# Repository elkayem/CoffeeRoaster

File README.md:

# COFFEE ROASTER

This repository contains the code for a PID controlled coffee roaster, run on a Teensy 3.5/3.6 development board.

A quick summary of the features:
* *Auto Mode* which will control the temperature (bean or environment) and fan speed to a settable profile.  
* *Manual Mode* where temperature and fan speed can be controlled in real time.
* Measured temperatures, set value, fan speed, and heater duty cycle saved to an SD card as a CSV file at 2 Hz while roasting.  See image above showing data from a roast.  I've also included a python script used to plot this data from the SD card.  The script requires the python module "matplotlib".  
* DC Fan PWM control.  (The MOSFET on the PCB can handle quite a bit of current.  I am using a 22 Amp, 260 Watt fan, and the MOSFET has additional headroom beyond that).    
* The roasting profile can be set as a sequence of up to 9 segments.  The set temperature and fan speed are linearly interpolated from one segment to the next.  This profile can be set and saved to EEPROM via the LCD screen interface.  
* Separate tuneable PID values for the environment temperature and bean temperature.  A tuning mode for each controller is available allowing one to monitor the step response and tune the gains in real time.
* (Optional) interface with [Artisan Roaster Scope](https://artisan-scope.org/).  The roast can be logged by Artisan in Auto or Manual mode, or even have Artisan control the set temperature and fan speed in Manual mode.  

I loosely based my roaster build off of a few of the fluid bed roasters over at the Home Roaster's forum using a Pyrex Bake-A-Round baking tube and inverted cocktail shaker lid.  For example, see Old Gear Head's fluid bed roaster design at: https://forum.homeroasters.org/forum/viewthread.php?thread_id=2207.   

Here are the parts needed for the electronics board:
* PCB (Order using gerber files in Eagle directory, or ask me and I'll send you one for a small amount.  Alternatively, the electronics can be soldered to a stripboard)
* Teensy 3.5 (or 3.6), $24.25 from pjrc.com + MicroSD card
* 2x MAX31855KASA+ thermocouple ICs ($5 each)
* 4x SMD ferrite beads (I used 470 ohms 0805 package)
* 3x BSS138 MOSFET transistors
* IRLB8721PBF MOSFET + heat sink (very important!!)
* 2N3904 transistor
* SB1245 Schottky diode
* 7805 5V regulator 
* Various resistors and capacitors (see schematic in Eagle directory)

Here are the additional parts I used:
* 20x4 character I2C LCD screen ($9 on eBay)
* Two K-type thermocouples
* Metal thermocouple probe shield (e.g., look for the 5mm x 50 mm thermocouple probe from Uxcell on Amazon, and cut off the end of the metal shield)
* Fotek SSR-40 DA Solid State Relay + Heat Sink ($12.50 on eBay)
* 12V, 25A power regulated switching power supply ($19 at eBay)
* Pyrex Bake-A-Round baking tube ($20 at eBay)
* Lid from Winco 16-oz coctail shaker, 1.5" and 3.5" diam ($7.50 at Amazon)
* 1.5" x 12" chrome tube ($10 at Amazon)
* HAS-043K 1700 Watt heating element ($22 at Amazon)
* Airhead "Air Pig" 12V, 22 Amp air pump ($42 at Amazon)
* 340 Silicone O-Rings 3.5" diam

A schematic and PCB design (see Eagle folder) is included in this repository.  The Gerber files can be uploaded to a PCB manufacturer (e.g., JLCPCB, SchenZhen2U, or Seeed Studio), typically for a few dollars a board and a minimum order of 5-10 boards.  Alternatively, contact me and I can send you one (without components) at cost plus shipping.  The electronics can also be soldered to a breadboard.  If using a breadboard, you will also need two MAX31855 breakout boards from Adafruit, as well as a logic level converter for the I2C LCD communication.

The DC motor is driven by the 12V power supply, with PWM speed control from the microcontroller.  It is vitally important that a few small capacitors be soldered directly to the motor leads to reduce voltage noise on the DC power, otherwise the inevitable voltage spikes from the DC motor will reset the microcontroller in the middle of your roast.  Not good!  I used a 22 nF capacitor across the leads, and then two 10 nF capacitors from each lead directly to the motor housing.   

The 12V, 22 Amp DC motor I used draws a lot of current, so be sure to use beefy wires (e.g., 14 AWG) all the way to the MOSFET.  Be sure to use a heat sink on the IRLB8721PBF MOSFET.  The wide traces on the back of the PCB are inadequate to handle 22A.  I recommend laying down a heavy layer of solder directly to these traces.  Better yet, solder exposed 14 AWG wire directly to the traces.  See photos above.

I enclosed the DC motor in my own 3D printed case and threw away the pig shaped case on the Airhead "Air Pig".  I've included the 3D printed case model in this repository, which encloses the motor and is sealed with a 3.5" O-ring.  I'm sure the pig shaped case would work too, but don't use the corrugated hose which produces too much drag.  

Two temperature measurements are used.  I placed the Environment Temperature thermocouple close to the center of the chamber in the line of fire of the hot air, and the Bean Temperature probe off to the side and blocked from the upcoming air.  A metal thermocouple shield is used to hold the probes in place.  I purchased a thermocouple probe from Uxcell on Amazon that came with a metal shield, and sawed off the end of the metal shield.  I have included a photograph below showing the thermocouple placement, and a drawing as well.  The bean temperature thermocouple and wires are taped to the top of the thermocouple metal shield using Kapton tape, which allows this thermocouple to register the temperature of the beans descending along the side of the shaker lid, and outside of the stream of hot air.  

I have also included a few 3D printed parts I used, which may be useful.  This repository includes a front panel for the LCD screen, and also the buttresses to hold the Bake-A-Round vertical. 

The plans for a 1/4" ply laser cut case are also included if you have access to a laser cutter.  Or build your own!  

# Artisan Roaster Scope Instructions
Artisan is not required for this roaster, as the Teensy firmware can already track a stored profile and save the roast data to an SD card without an external interface.  I still highly recommend Artisan as it includes additional visual analysis tools. 

**Important Note:** The USB port 5V power *must* be disconnected before attempting to interface with Artisan. There are several ways to do this, described at https://www.pjrc.com/teensy/external_power.html.  The simplest way is to disconnect the 5V pads apart on the bottom of the Teensy board.  I chose a different method in my roaster.  My roaster has a USB panel mount on the outside of the case, with an internal USB cable going from the panel mount to the Teensy.  Since this cable is permanently isntalled inside my case, I chose to clip the red wire inside the cable, sealing off the cut wire with shrink tube to prevent a short.  This avoids the need to modify the Teensy itself.

Coffee Roaster uses the same Artisan communication protocol as a TC4.  To use this Teensy code with Artisan, set up the device as a TC4 in Config>Device on the ET/BT tab.  Check the "Control" and "PID Firmware" checkboxes.  On the Extra Devices tab, set up the ArduinoTC4_34, ArduinoTC4_56 (Label 1 = Heater, Label 2 = Fan), and ArduinoTC4_78 (Label 1 = SV, Label 2 = Ambient).  Check the LCD 1, LCD 2, Curve 1, and Curve 2 checkboxes for ArduinoTC4_56 and _78, but uncheck for _34.  The YouTube video [Artisan Roaster Scope - Setup for TC4](https://youtu.be/0-Co-pXF2NM) walks through the setup procedure.

The above steps are sufficient for logging your roast with Artisan.  To control the roast using Artisan, check out the YouTube video [Artisan Roaster Scope - TC4 PID Control](https://youtu.be/ykuUCXhGAC4).  This video has four parts.  The two parts labeled "Background Follow TC4 PID" and "Ramp/Soak Profile TC4 PID" can be used with this code.  The "Artisan PID" variants are not currently supported.  

If using Artisan to control your roaster, you will also need to set up the DC Fan control. To do this, open the Config>Events dialog, change the first Event name to Fan, go to the Sliders tab, and set the Fan Action to Serial Command, and add the command "DCFAN;{}" to the selection box, without the quotes.

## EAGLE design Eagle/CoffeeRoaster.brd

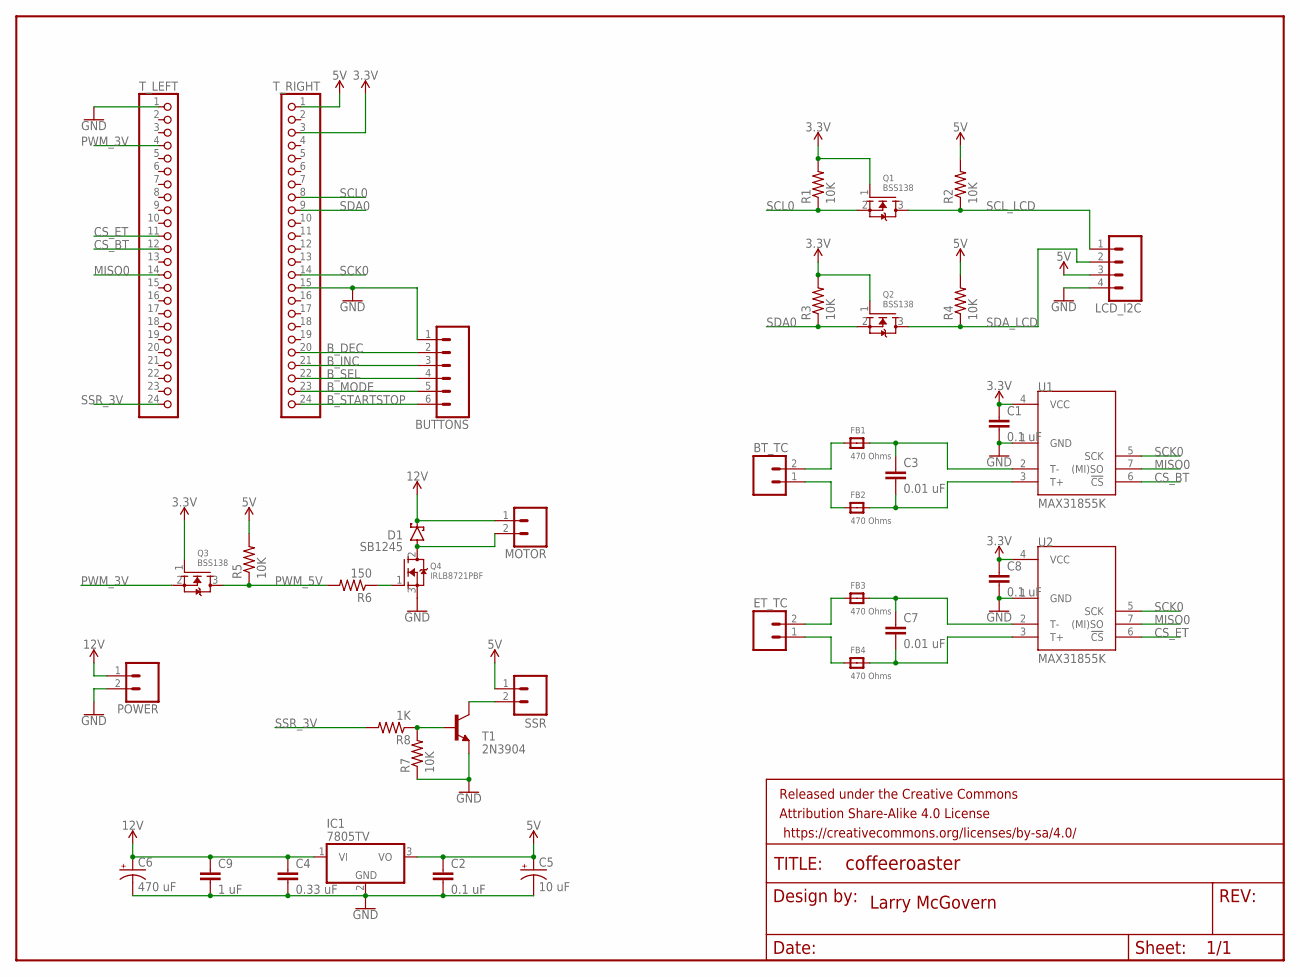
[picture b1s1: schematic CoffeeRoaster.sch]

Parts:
BT_TC: M025MM; SCREWTERMINAL-5MM-2
BUTTONS: CONN_06SILK_FEMALE_PTH; 1X06
C1, C2, C8: 0.1 uF; C050-025X075
C3, C7: 0.01 uF; C050-025X075
C4: 0.33 uF; C050-025X075
C5: 10 uF; E2,5-6
C6: 470 uF; E5-10,5
C9: 1 uF; C050-025X075
D1: SB1245; DO201T15
ET_TC: M025MM; SCREWTERMINAL-5MM-2
FB1, FB2, FB3, FB4: 470 Ohms; _0805
FRAME1: FRAME-LETTER; CREATIVE_COMMONS
IC1: 7805TV; TO220V
LCD_I2C: CONN_04; 1X04
MOTOR: CONN_02PTH4; 1X02_XTRA_BIG
POWER: CONN_02PTH4; 1X02_XTRA_BIG
Q1, Q2, Q3: BSS138; SOT23
Q4: IRLB8721PBF; TO220V
R1, R2, R3, R4, R5, R7: 10K; 0207/10
R6: 150; 0207/10
R8: 1K; 0207/10
SSR: M025MM; SCREWTERMINAL-5MM-2
T1: 2N3904; TO92
T_LEFT: PINHD-1X24; 1X24
T_RIGHT: PINHD-1X24; 1X24
U1, U2: MAX31855K; SO08

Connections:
3.3V: C1.1, C8.1, Q1.1 (G), Q2.1 (G), Q3.1 (G), R1.2, R3.2, T_RIGHT.3, U1.4 (VCC), U2.4 (VCC)
5V: C2.1, C5.+, IC1.3 (VO), LCD_I2C.3, R2.2, R4.2, R5.2, SSR.1, T_RIGHT.1
12V: C4.1, C6.+, C9.1, D1.C, IC1.1 (VI), MOTOR.1, POWER.1
B_DEC: BUTTONS.2, T_RIGHT.20
B_INC: BUTTONS.3, T_RIGHT.21
B_MODE: BUTTONS.5, T_RIGHT.23
B_SEL: BUTTONS.4, T_RIGHT.22
B_STARTSTOP: BUTTONS.6, T_RIGHT.24
CS_BT: T_LEFT.12, U1.6 (!CS)
CS_ET: T_LEFT.11, U2.6 (!CS)
GND: BUTTONS.1, C1.2, C2.2, C4.2, C5.-, C6.-, C8.2, C9.2, IC1.2 (GND), LCD_I2C.4, POWER.2, Q4.3 (S), R7.1, T1.3 (E), T_LEFT.1, T_RIGHT.15, U1.1 (GND), U2.1 (GND)
MISO0: T_LEFT.14, U1.7 ((MI)SO), U2.7 ((MI)SO)
MOT_NEG: D1.A, MOTOR.2, Q4.2 (D)
unnamed: Q4.1 (G), R6.1
unnamed: BT_TC.2, FB1.1
unnamed: ET_TC.2, FB3.1
unnamed: C3.1, FB1.2, U1.2 (T-)
unnamed: BT_TC.1, FB2.1
unnamed: C3.2, FB2.2, U1.3 (T+)
unnamed: C7.1, FB3.2, U2.2 (T-)
unnamed: ET_TC.1, FB4.1
unnamed: C7.2, FB4.2, U2.3 (T+)
unnamed: R7.2, R8.1, T1.2 (B)
unnamed: SSR.2, T1.1 (C)
PWM_3V: Q3.2 (S), T_LEFT.4
PWM_5V: Q3.3 (D), R5.1, R6.2
SCK0: T_RIGHT.14, U1.5 (SCK), U2.5 (SCK)
SCL0: Q1.2 (S), R1.1, T_RIGHT.8
SCL_LCD: LCD_I2C.1, Q1.3 (D), R2.1
SDA0: Q2.2 (S), R3.1, T_RIGHT.9
SDA_LCD: LCD_I2C.2, Q2.3 (D), R4.1
SSR_3V: R8.2, T_LEFT.24

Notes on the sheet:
Larry McGovern

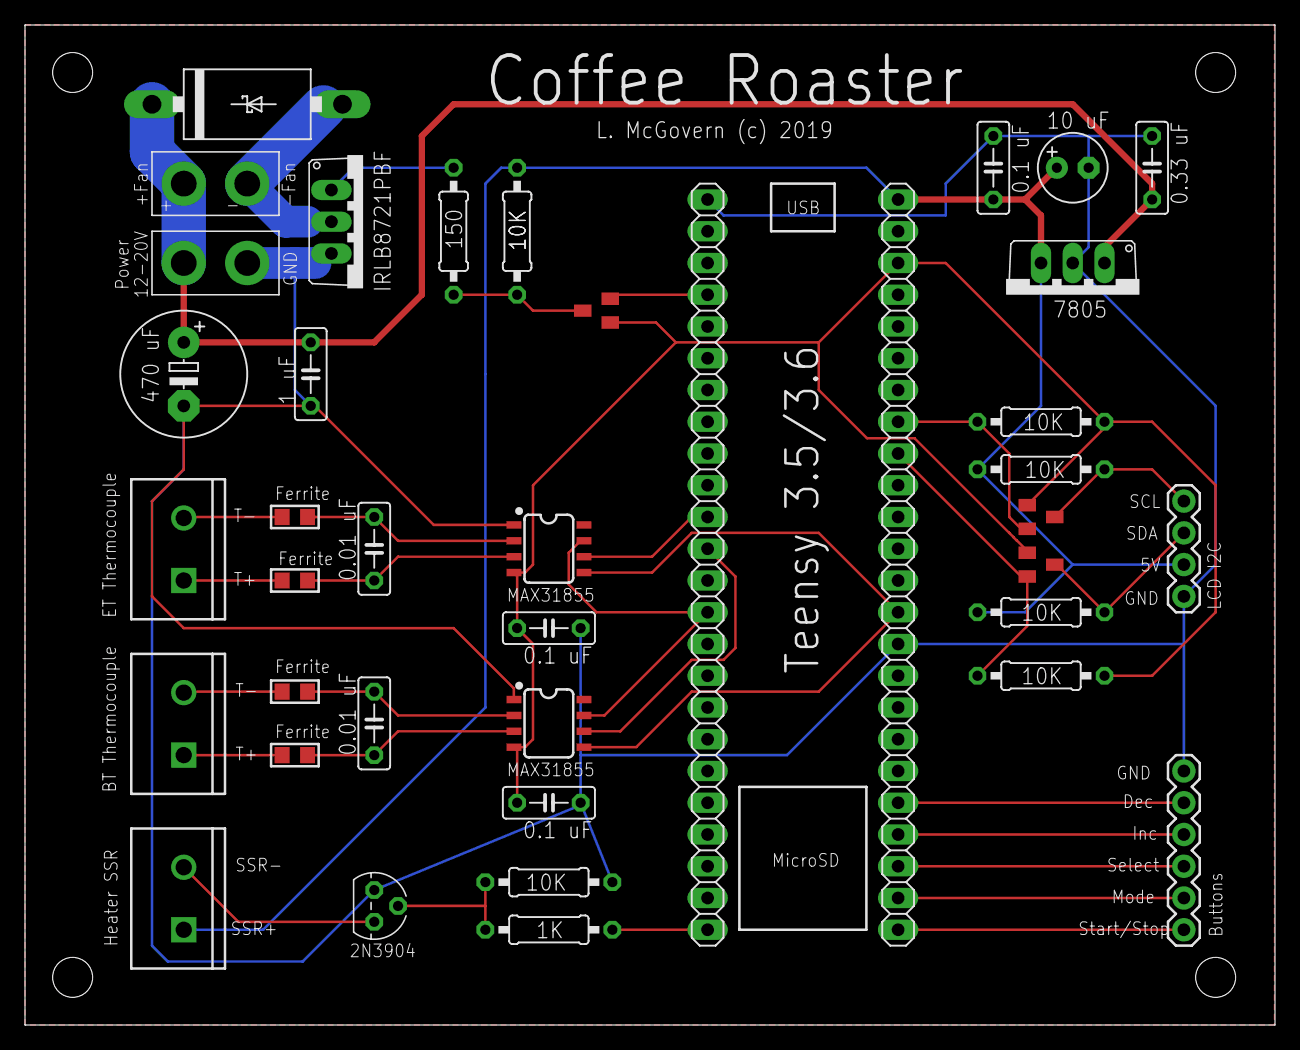
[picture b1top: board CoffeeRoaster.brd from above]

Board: 2 copper layers, 100.0 x 80.0 mm, 40 parts (0 on the bottom side), 32 nets.

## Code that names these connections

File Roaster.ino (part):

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#include "Adafruit_MAX31856.h"
#include <Bounce2.h>

#define B_STARTSTOP PB12
#define B_MODE      PB13
#define B_SEL       PB14
#define B_INC       PB15
#define B_DEC       PA8
#define FAN_PWM     PA1
#define SD_CS       PB0
#define ENVTEMP_CS  PA3
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
void setup() {
  Serial.begin(115200);
  pinMode(B_STARTSTOP, INPUT_PULLUP);
  pinMode(B_MODE, INPUT_PULLUP);
  pinMode(B_SEL, INPUT_PULLUP);
  pinMode(B_INC, INPUT_PULLUP);
  pinMode(B_DEC, INPUT_PULLUP);

  pinMode(HEATER, OUTPUT);
  digitalWrite(HEATER, LOW);
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
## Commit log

2018-02-26 Initial checkin
2018-02-28 Add 2nd pid loop
2018-02-28 prepare for auto mode
2018-02-28 auto settings saved to EEPROM
2018-03-02 Add profile
2018-03-03 minor tweaks
2018-03-06 Derivative FIR filter
2018-03-09 Update defaults
2018-03-09 Add README and additional files
2018-03-09 Coffee photo
2018-03-10 minor fix
2018-03-17 modify set temperature data type
2018-08-24 Updated for new roaster design.
2018-12-26 Add drawing showing thermocouple placement. Add python script for plotting profile.
2018-12-29 Update images showing thermocouple placement
2019-02-23 Updates for Teensy 3.5
2019-03-02 Add Artisan roaster scope support
2019-03-03 Updated README for details on Artisan
2019-03-08 End of roast improvements
2019-05-31 Modify end of roast logic

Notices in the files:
Eagle/CoffeeRoaster.brd:
L. McGovern (c) 2019
parts and their libraries:
SparkFun-IC-Conversion: Licensing: Creative Commons ShareAlike 4.0 International - https://creativecommons.org/licenses/by-sa/4.0
SparkFun-Aesthetics: Released under the Creative Commons Attribution Share-Alike 4.0 License
SparkFun-Aesthetics: https://creativecommons.org/licenses/by-sa/4.0
